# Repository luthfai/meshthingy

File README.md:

# meshthingy

> An off-grid LoRa mesh communicator — a pocket-sized ESP32-S3 node that sends
> text and GPS position over kilometres of open ground, with no cell tower, no
> SIM, no subscription, and no internet.

<sub>KiCad 10 · 2-layer · 71 × 46 mm · ESP32-S3 + SX1262 LoRa · USB-C · Li-Ion · hardware rev R1</sub>

> [!WARNING]
> **Rev R1 is currently in fabrication — nothing here has been tested yet.**
> The schematic and layout are finished and pass DRC, but no board has been
> assembled or powered up. Everything in this README (pin map, charger settings,
> power latch behaviour, assembly notes) describes the design *as intended* and
> may change after bring-up. Build one at your own risk.

## Project status

| Stage | Status |
| --- | --- |
| Schematic | ✅ Done |
| PCB layout | ✅ Done — 0 DRC violations, 0 unconnected items |
| BOM | ✅ Done — a few part variants still to pick (see [Bill of materials](#bill-of-materials)) |
| PCB fabrication | ⏳ In progress |
| Assembly | ⬜ Not started |
| Bring-up and testing | ⬜ Not started |
| Firmware | 🚧 Work in progress |

---

## What this board is for

Phones stop working the moment you leave coverage. **meshthingy** doesn't need
coverage — it *is* the network.

Each board is one node in a self-healing [Meshtastic](https://meshtastic.org)
mesh. Nodes talk directly to each other over licence-free LoRa radio, and every
node automatically relays traffic for its neighbours. Two units give you a
private long-range walkie-talkie for text; a handful scattered across a valley,
a campsite, a ridgeline, or a city block give everyone in that area a shared
messaging network that keeps working when nothing else does.

Because LoRa trades bandwidth for range and power, a node runs for **days** on a
small Li-Ion cell and reaches **several kilometres** line-of-sight — far past
Wi-Fi or Bluetooth, and without the power budget a cellular radio demands.

Typical uses: hiking and backcountry trips, sailing, off-road convoys, festival
and event crews, neighbourhood emergency preparedness, and as a low-cost
long-range telemetry link for remote sensors.

The onboard GPS, environmental and motion sensors mean a node is useful even
with nobody holding it — drop one on a hilltop as a solar-powered repeater and
it becomes a weather station that also extends everyone's range.

## Features

- **ESP32-S3-WROOM-1** — dual-core MCU with Wi-Fi and Bluetooth LE for phone pairing, native USB
- **HT-RA62 LoRa module** (SX1262) — long-range sub-GHz radio on an SMA edge-mount connector
- **ATGM336H GNSS** — position reporting on a U.FL active antenna, with a rechargeable backup cell for warm starts
- **0.96" OLED** — read messages without a phone
- **BME280** — temperature, humidity, barometric pressure, on a slotted island away from board heat
- **LIS3DSH accelerometer** — wake-on-motion and orientation, with interrupt to the MCU
- **USB-C charging** — BQ24072 Li-Ion charger with power-path, so it runs while charging
- **Soft power switch** — the lever's push turns the node on; firmware holds power and can turn itself off
- **JST-PH battery connector** — standard single-cell Li-Ion / LiPo, polarity marked on the silkscreen
- **Vibration motor driver** — SI2302 low-side switch with flyback diode, for silent alerts in a pocket
- **Buzzer, status LED, and a side lever switch** (CW / CCW / push) for headless operation
- **Test points** on every bus for bring-up and debugging

## System architecture

```mermaid
flowchart TB
    subgraph RF["📡 Radio"]
        LORA["<b>U4 · HT-RA62</b><br/>SX1262 LoRa"]
        SMA["J4 · SMA<br/>edge mount"]
        LORA --- SMA
    end

    subgraph CORE["🧠 Core"]
        MCU["<b>U7 · ESP32-S3-WROOM-1</b><br/>Wi-Fi · BLE · dual core"]
    end

    subgraph NAV["🛰️ Navigation"]
        GPS["<b>U2 · ATGM336H</b><br/>GNSS receiver"]
        UFL["J3 · U.FL<br/>active antenna"]
        EEP["U8 · AT24CS32<br/>EEPROM"]
        BAT2["C13 · XH414H<br/>backup cell"]
        UFL --- GPS
        GPS -->|"private I²C"| EEP
        BAT2 -.->|"keeps time"| GPS
    end

    subgraph IO["🔌 I²C peripherals"]
        OLED["U1 · 0.96in OLED"]
        BME["U9 · BME280<br/>temp · humidity · pressure"]
        ACC["U10 · LIS3DSH<br/>accelerometer"]
    end

    subgraph UX["🎛️ Interface"]
        BUZ["LS1 · buzzer"]
        LED["D2 · status LED"]
        SW["U5 · lever switch"]
        VIB["Q4 · SI2302<br/>vibration motor"]
    end

    MCU <==>|"<b>SPI</b> + BUSY/RST/DIO1"| LORA
    MCU <-->|"<b>UART</b> + 1PPS"| GPS
    MCU <-->|"<b>I²C</b> · IO13/IO14"| OLED
    MCU <-->|"<b>I²C</b>"| BME
    MCU <-->|"<b>I²C</b> + INT→IO48"| ACC
    MCU -->|IO16| BUZ
    MCU -->|IO21| LED
    MCU -->|IO15| VIB
    SW -->|"IO10/11/12"| MCU

    classDef core fill:#4f46e5,stroke:#3730a3,color:#fff,stroke-width:2px
    classDef radio fill:#0891b2,stroke:#0e7490,color:#fff
    classDef nav fill:#059669,stroke:#047857,color:#fff
    classDef periph fill:#d97706,stroke:#b45309,color:#fff
    classDef ux fill:#7c3aed,stroke:#6d28d9,color:#fff
    class MCU core
    class LORA,SMA radio
    class GPS,UFL,EEP,BAT2 nav
    class OLED,BME,ACC periph
    class BUZ,LED,SW,VIB ux
```

## Power path

USB-C and the battery both feed a power-path charger, so the node keeps running
while it charges and switches over seamlessly when USB is unplugged. The 3.3 V
buck converter is only enabled while something holds the power latch on.

```mermaid
flowchart LR
    USB["<b>J1</b><br/>USB-C<br/>5 V in"] -->|VBUS| CHG
    BATT["<b>J2</b><br/>Li-Ion cell<br/>JST-PH"] <-->|charge / discharge| CHG
    CHG["<b>U6 · BQ24072</b><br/>Li-Ion charger<br/>+ power path"] -->|VSYS| BUCK
    LATCH["<b>Power latch</b><br/>Q2 · Q3"] -->|BUCK_EN| BUCK
    BUCK["<b>U3 · TPS62046</b><br/>3.3 V step-down<br/>via L2"] -->|"+3V3"| RAIL

    BTN["Lever push"] -.-> LATCH
    PG["USB present<br/>(PGOOD)"] -.-> LATCH
    HOLD["IO9 · SYS_EN<br/>(firmware hold)"] -.-> LATCH

    RAIL["<b>+3V3 rail</b>"] --> M1["ESP32-S3"]
    RAIL --> M2["LoRa"]
    RAIL --> M3["GNSS"]
    RAIL --> M4["Sensors + OLED"]
    RAIL --> M5["Buzzer + vib motor"]

    classDef src fill:#dc2626,stroke:#991b1b,color:#fff,stroke-width:2px
    classDef conv fill:#ea580c,stroke:#c2410c,color:#fff,stroke-width:2px
    classDef rail fill:#16a34a,stroke:#15803d,color:#fff,stroke-width:2px
    classDef load fill:#475569,stroke:#334155,color:#fff
    classDef ctl fill:#64748b,stroke:#475569,color:#fff
    class USB,BATT src
    class CHG,BUCK conv
    class RAIL rail
    class M1,M2,M3,M4,M5 load
    class LATCH,BTN,PG,HOLD ctl
```

### Turning on and off

The buck converter's enable is driven by a PNP switch (`Q2`) from a latch node
that is pulled low by any one of three sources, each isolated by a 1N4148WS:

1. **Lever push** (`U5`, `D7`) — pressing it powers the board up.
2. **USB present** (`PGOOD` from `U6`, `D4`) — the node is always on while plugged in.
3. **Firmware hold** (`IO9` / `SYS_EN` through `Q3`) — firmware must drive IO9 high
   early in boot, or the board switches off again when the lever is released.
   Driving IO9 low (with USB unplugged) powers the node down.

The MCU can read the lever push on `IO10` and USB presence on `IO17` (both through
diodes, active low, use internal pull-ups). The latch diodes must stay
low-leakage silicon parts — Schottkys leak enough to half-enable the buck when off.

### Charger settings (U6 · BQ24072)

| Setting | Part | Value |
| --- | --- | --- |
| Fast-charge current | `R4` = 1k (1%) | ≈ 890 mA |
| USB input current limit | `R5` = 1k2, EN2 = 1 / EN1 = 0 | ≈ 1.34 A |
| Safety timers | `R6` = 47k | pre-charge ≈ 38 min, fast charge ≈ 6.3 h |
| Termination | `TD` tied low | enabled |
| Battery temperature | `R3` = 10k fixed on `TS` | no thermistor, sensing disabled |
| Charge enable | `IO18` (`R7` pull-down) | low = charging allowed |

`VSYS` follows the battery (and tracks VBAT + 225 mV while charging). `IO8` reads
`VSYS / 2` through `R16`/`R17` — that is the battery voltage when running on battery.

## Board

| | |
| --- | --- |
| **Dimensions** | 71.0 × 46.0 mm, cut-out under the ESP32 antenna, milled slots isolating the BME280 |
| **Stackup** | 2 layers (F.Cu / B.Cu), 1.6 mm |
| **Components** | 96 footprints, 353 pads (329 SMD, 22 through-hole, 2 NPTH), 378 vias |
| **Density** | 66% front, 9% back — almost everything lives on the front |
| **Copper** | GND pour on both layers, pour cut back under the RF connectors and antennas |
| **Design rules** | 0.175 mm clearance, 0.2 mm minimum track, 0.6 / 0.3 mm vias |
| **Assembly** | SMD on the front, 0805 passives; through-hole only for `J2`, the OLED header and the USB-C shell tabs |

Everything routes on two layers, which keeps this a cheap board to order from any
prototype fab at standard tolerances.

### Assembled views

<table>
  <tr>
    <td width="50%" align="center">
      <br>
      <sub><b>Front</b> — LoRa and GNSS modules, ESP32-S3, USB-C, buzzer, GPS backup cell, motor driver</sub>
    </td>
    <td width="50%" align="center">
      <br>
      <sub><b>Back</b> — labelled test points for every bus, vibration motor pads (<code>JP1</code>, silkscreen <code>VBR</code>), repo QR code</sub>
    </td>
  </tr>
</table>

### PCB layer views

Copper, silkscreen and board outline, plotted straight from the layout. The back
view is mirrored so its silkscreen reads the right way round.

<table>
  <tr>
    <td width="50%" align="center">
      <br>
      <sub><b>F.Cu + F.SilkS</b> — signal routing over the front ground pour; <code>B</code>/<code>R</code> are the boot and reset pads</sub>
    </td>
    <td width="50%" align="center">
      <br>
      <sub><b>B.Cu + B.SilkS</b> — mirrored; back pour with the test-point field and motor pads</sub>
    </td>
  </tr>
</table>

The RF section is deliberately sparse: the pours are cut back under the antenna
connectors, the ESP32's PCB antenna hangs over a board cut-out, and the GPS
keepout is marked on the silkscreen so nothing gets placed under it during assembly.

Regenerate the 3D renders and layer plots after any layout change (the renders
are trimmed with ImageMagick):

```bash
kicad-cli pcb render --output /tmp/f.png --side top    --quality high --width 2000 --height 1300 meshthingy.kicad_pcb
kicad-cli pcb render --output /tmp/b.png --side bottom --quality high --width 2000 --height 1300 meshthingy.kicad_pcb
magick /tmp/f.png -trim +repage -bordercolor none -border 24 docs/meshthingy-f.png
magick /tmp/b.png -trim +repage -bordercolor none -border 24 docs/meshthingy-b.png

kicad-cli pcb export svg --output docs/layers-front.svg \
  --layers "F.Cu,F.SilkS,Edge.Cuts" \
  --page-size-mode 2 --exclude-drawing-sheet --check-zones --mode-single \
  meshthingy.kicad_pcb

kicad-cli pcb export svg --output docs/layers-back.svg \
  --layers "B.Cu,B.SilkS,Edge.Cuts" --mirror \
  --page-size-mode 2 --exclude-drawing-sheet --check-zones --mode-single \
  meshthingy.kicad_pcb
```

## Pin map

| Function | ESP32-S3 pin | Goes to |
| --- | --- | --- |
| LoRa SCK | GPIO43 (TXD0) | `U4` pin 12 SCK |
| LoRa MOSI | IO1 | `U4` pin 14 MOSI |
| LoRa MISO | IO2 | `U4` pin 13 MISO |
| LoRa CS | IO6 | `U4` pin 15 NSS |
| LoRa DIO1 | IO4 | `U4` pin 6 (IRQ) |
| LoRa RESET | IO5 | `U4` pin 4 |
| LoRa BUSY | GPIO44 (RXD0) | `U4` pin 10 |
| GPS TX → MCU RX | IO42 | `U2` TXD |
| GPS RX ← MCU TX | IO41 | `U2` RXD |
| GPS 1PPS | IO40 | `U2` 1PPS |
| GPS reset | IO38 | `U2` nRESET |
| GPS on/off | IO39 | `U2` ON/OFF |
| I²C SDA / SCL | IO13 / IO14 | OLED (0x3C), BME280 (0x76), LIS3DSH (0x1D) |
| Accelerometer INT | IO48 | `U10` INT1 |
| Lever push | IO10 | `U5` push, via `D6` (active low) |
| Lever CCW / CW | IO11 / IO12 | `U5` (active low, 100 nF debounce) |
| Power hold | IO9 | `Q3` via `R9` — drive high to stay on |
| USB present | IO17 | `U6` PGOOD via `D3` (active low) |
| Charge enable | IO18 | `U6` CE (low = charge) |
| Battery sense | IO8 (ADC1_CH7) | `VSYS / 2` |
| Vibration motor | IO15 | `Q4` gate (10k pull-down `R23`) |
| Buzzer | IO16 | `Q1` gate (10k pull-down `R11`) |
| Status LED | IO21 | `D2` via `R22` |
| USB D− / D+ | IO19 / IO20 | `J1` (native USB) |
| Boot / reset | IO0 / EN | `B` / `R` pads |
| Spare / test | IO7, IO47 | back-side test points `IO07`, `IO47` |

IO3, IO35–37, IO45 and IO46 are left unconnected (strapping pins and the
octal-PSRAM pins on R8 module variants).

## Schematic layout

The design is hierarchical — root sheet [meshthingy.kicad_sch](meshthingy.kicad_sch):

| Sheet | Contents |
| --- | --- |
| [Power Management](Power%20Management.kicad_sch) | BQ24072 charger, TPS62046 buck, power latch, battery sense |
| [Microcontroller](Microcontroller.kicad_sch) | ESP32-S3-WROOM-1, boot and reset pads |
| [LORA](LORA.kicad_sch) | HT-RA62 module and SMA antenna path |
| [GPS](GPS.kicad_sch) | ATGM336H, U.FL antenna input, EEPROM, backup cell |
| [Display](Display.kicad_sch) | 0.96" OLED and its pinout-select jumpers |
| [Air Sensors](Air%20Sensors.kicad_sch) | BME280 |
| [Accelerometer](Accelerometer.kicad_sch) | LIS3DSH |
| [Peripherals](Peripherals.kicad_sch) | Buzzer and vibration motor drivers, status LED, test points |
| [Connectors](Connectors.kicad_sch) | USB-C receptacle, JST-PH battery |

## Bill of materials

The curated BOM is [bom/meshthingy-bom.csv](bom/meshthingy-bom.csv): 36 board
lines / 76 placed parts, plus the off-board items (battery, antennas, vibration
motor). It adds manufacturer part numbers where the footprint fixes the part,
and a notes column with ratings and the reason behind each value.

Still to pin down before ordering parts:

- `U7` — pick the module variant (e.g. `-N8R2`, `-N16R8`). Avoid the 1.8 V `…V`
  variants: IO47 and IO48 are in use.
- `C16`, `C25` — voltage rating (≥ 10 V low-ESR tantalum).
- `U4` — `HT-RA62-HF` for 863–928 MHz, `HT-RA62-LF` for 433/470 MHz.

Test points and solder jumpers are left out — they are PCB features, not parts.

A print-ready A4 copy with kitting checkboxes and the open items highlighted is
rendered from the CSV with `python bom/render_bom_pdf.py` (needs `pip install weasyprint`)
and written to `bom/meshthingy-bom.pdf`. For hand assembly, open
[bom/ibom.html](bom/ibom.html) in a browser — an interactive BOM that highlights
each part's position on the board.

## Building it

Open [meshthingy.kicad_pro](meshthingy.kicad_pro) in **KiCad 10** or newer.
All custom symbols and footprints live in [libs/](libs/) and are referenced through
`${KIPRJMOD}`, so the project is self-contained — clone and open, nothing else to install.

Generate fabrication files from the command line:

```bash
# Gerbers + drill, ready to zip and upload to a fab
kicad-cli pcb export gerbers --output fab/ meshthingy.kicad_pcb
kicad-cli pcb export drill   --output fab/ meshthingy.kicad_pcb

# Raw schematic BOM and pick-and-place
kicad-cli sch export bom       --output fab/bom-raw.csv meshthingy.kicad_sch
kicad-cli pcb export pos       --output fab/pos.csv meshthingy.kicad_pcb

# Design rules check
kicad-cli pcb drc --output fab/drc.rpt meshthingy.kicad_pcb
```

Generated outputs are gitignored — regenerate them, or attach them to a release tag.

### Assembly notes

`U3` (TPS62046) has a PowerPAD that must be soldered to the ground pad under it.
The pad is a copper shape on the board rather than part of the footprint, so it has
no paste aperture — tin it by hand, or add paste to the stencil, before reflowing U3.

`JP3` and `JP4` are three-way solder jumpers that select which OLED pin gets
`+3V3` and which gets `GND`, so the footprint accepts display modules with either
pinout. They ship **unbridged** — bridge them to match the module you source
before expecting the display to light up. Never bridge all three pads of one jumper.

`JP1` on the back (silkscreen `VBR`) is not a jumper. It's the pair of solder pads for the vibration
motor. Solder a coin or pager-style motor's leads across it: the pad on the
`+3V3` side takes the red lead and the pad on the `Q4` drain side takes the black
lead. `D9` clamps the motor's flyback, so the motor runs straight off the
`+3V3` rail.

`J2` has `+` / `−` marked on both sides. JST-PH battery leads are not wired the same
way by every vendor, and there is no reverse-polarity protection — check the plug
before connecting a cell.

`B` and `R` on the front are the **BOOT** and **RESET** pads. To put the ESP32-S3
into the ROM bootloader, short `B` while you tap `R`.

## Firmware

🚧 **Work in progress.** There is no firmware for this board yet — it will target
[Meshtastic](https://meshtastic.org) on the ESP32-S3 once the first boards are
back from the fab and brought up. Until then, the [pin map](#pin-map) above is
the reference for anyone writing a variant.

## Repository notes

`.history/` is KiCad 10's Local History — a separate nested git repository of
autosaves. It is gitignored and should stay that way. Delete it freely if you
don't need the local undo history.

---

<sub>Meshtastic® is a registered trademark of Meshtastic LLC. This is an
independent hardware design and is not affiliated with or endorsed by Meshtastic LLC.</sub>

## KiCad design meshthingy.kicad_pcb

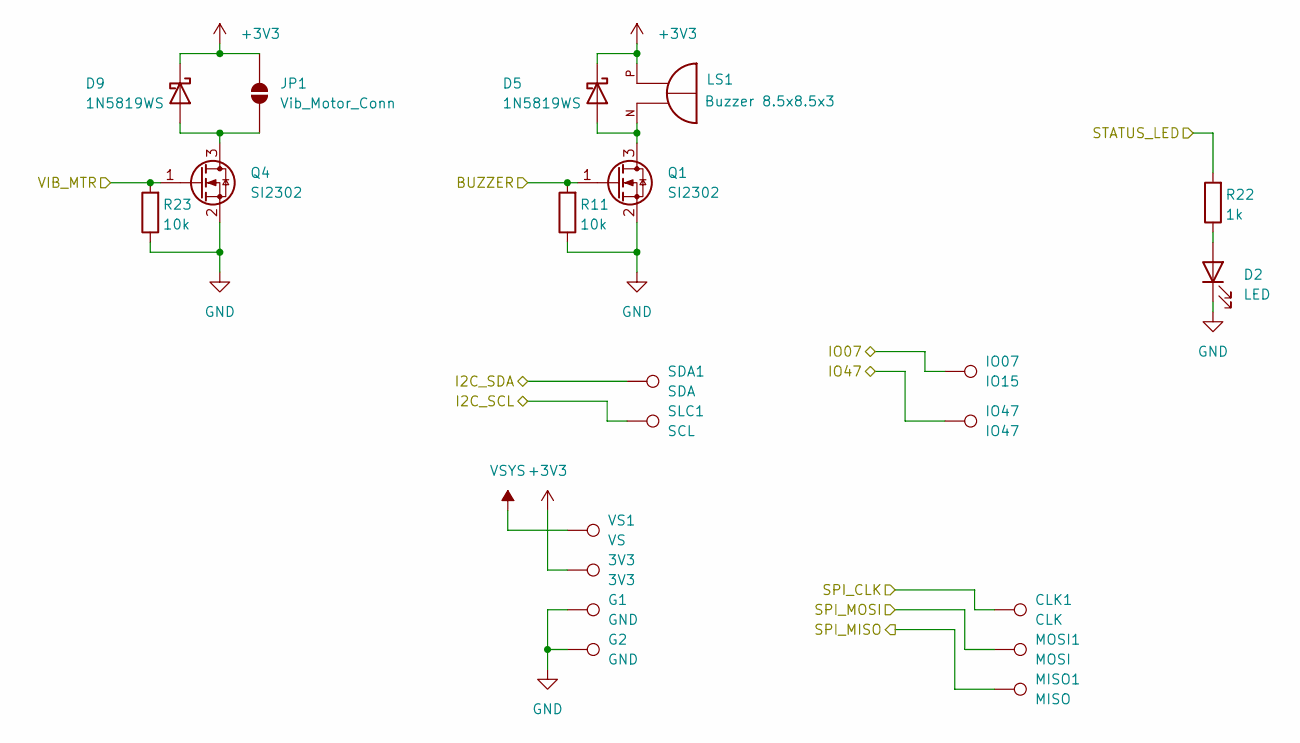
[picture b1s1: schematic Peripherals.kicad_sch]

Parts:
3V3: 3V3; TestPoint_Pad_1.0x1.0mm
CLK1: CLK; TestPoint_Pad_1.0x1.0mm
D2: LED; LED_0805_2012Metric
D5, D9: 1N5819WS; D_SOD-323
G1, G2: GND; TestPoint_Pad_1.0x1.0mm
IO07: IO15; TestPoint_Pad_1.0x1.0mm
IO47: IO47; TestPoint_Pad_1.0x1.0mm
JP1: Vib_Motor_Conn; SolderJumper-2_P1.3mm_Open_Pad1.0x1.5mm
LS1: Buzzer 8.5x8.5x3; XDCR_SMT-0927-S-14-R; PARTREV A
MISO1: MISO; TestPoint_Pad_1.0x1.0mm
MOSI1: MOSI; TestPoint_Pad_1.0x1.0mm
Q1, Q4: SI2302; SOT-23
R11, R23: 10k; R_0805_2012Metric
R22: 1k; R_0805_2012Metric
SDA1: SDA; TestPoint_Pad_1.0x1.0mm
SLC1: SCL; TestPoint_Pad_1.0x1.0mm
VS1: VS; TestPoint_Pad_1.0x1.0mm

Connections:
+3V3: 3V3.1 (1_1), D5.1 (K), D9.1 (K), JP1.2 (B), LS1.P; also elsewhere on the board
/Accelerometer/SCL: SLC1.1 (1_1); also elsewhere on the board
/Accelerometer/SDA: SDA1.1 (1_1); also elsewhere on the board
/LORA/SPI2_CLK: CLK1.1 (1_1); also elsewhere on the board
/LORA/SPI2_MISO: MISO1.1 (1_1); also elsewhere on the board
/LORA/SPI2_MOSI: MOSI1.1 (1_1); also elsewhere on the board
/Microcontroller/BUZZER: Q1.1 (G), R11.2; also elsewhere on the board
/Microcontroller/IO07: IO07.1 (1_1); also elsewhere on the board
/Microcontroller/IO47: IO47.1 (1_1); also elsewhere on the board
/Microcontroller/STATUS_LED: R22.2; also elsewhere on the board
/Microcontroller/VIB_MTR: Q4.1 (G), R23.2; also elsewhere on the board
GND: D2.1 (K), G1.1 (1_1), G2.1 (1_1), Q1.2 (S), Q4.2 (S), R11.1, R23.1; also elsewhere on the board
unnamed: D2.2 (A), R22.1
unnamed: D5.2 (A), LS1.N, Q1.3 (D)
unnamed: D9.2 (A), JP1.1 (A), Q4.3 (D)
VSYS: VS1.1 (1_1); also elsewhere on the board

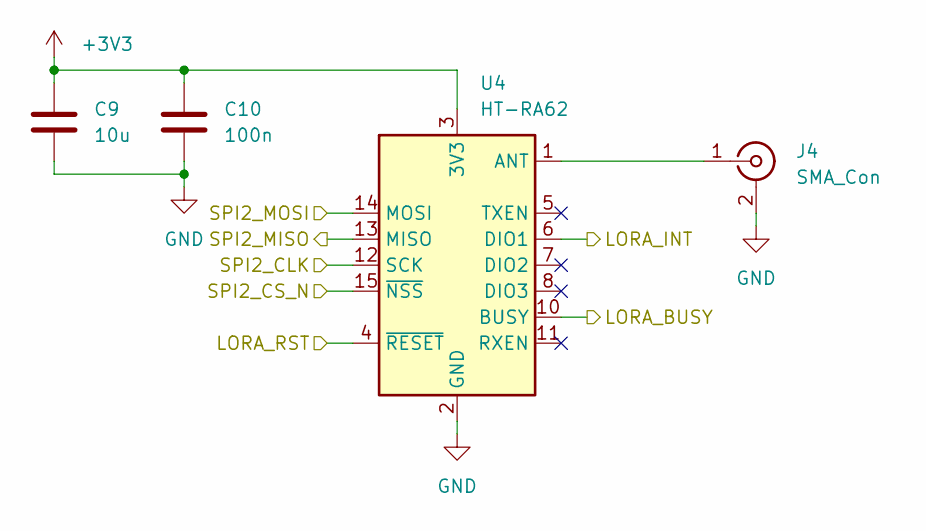
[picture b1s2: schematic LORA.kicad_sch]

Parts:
C9: 10u; C_0805_2012Metric
C10: 100n; C_0805_2012Metric
J4: SMA_Con; SMA_Amphenol_132289_EdgeMount
U4: HT-RA62; Ai-Thinker-Ra-01-LoRa

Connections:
+3V3: C9.1, C10.1, U4.3 (3V3); also elsewhere on the board
/LORA/LORA_BUSY: U4.10 (BUSY); also elsewhere on the board
/LORA/LORA_INT: U4.6 (DIO1); also elsewhere on the board
/LORA/LORA_RST: U4.4 (~RESET); also elsewhere on the board
/LORA/SPI2_CLK: U4.12 (SCK); also elsewhere on the board
/LORA/SPI2_CS_N: U4.15 (~NSS); also elsewhere on the board
/LORA/SPI2_MISO: U4.13 (MISO); also elsewhere on the board
/LORA/SPI2_MOSI: U4.14 (MOSI); also elsewhere on the board
GND: C9.2, C10.2, J4.2 (Ext), U4.2 (GND), U4.9 (GND), U4.16 (GND); also elsewhere on the board
unnamed: J4.1 (In), U4.1 (ANT)

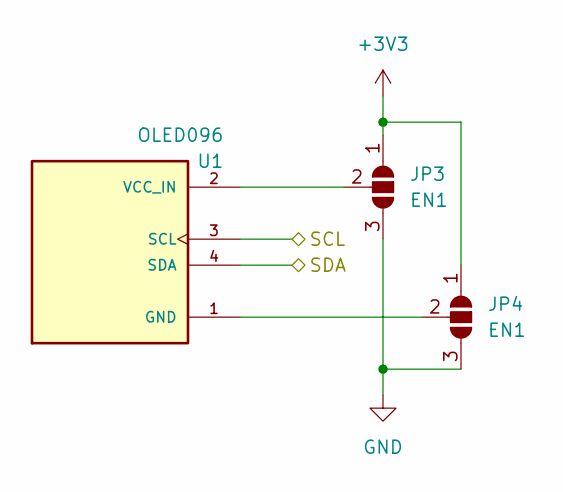
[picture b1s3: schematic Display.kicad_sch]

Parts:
JP3, JP4: EN1; SolderJumper-3_P1.3mm_Open_Pad1.0x1.5mm
U1: OLED096; MODULE_DM-OLED096-636; PARTREV 2018-09-10

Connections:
+3V3: JP3.1 (A), JP4.1 (A); also elsewhere on the board
/Accelerometer/SCL: U1.3 (SCL); also elsewhere on the board
/Accelerometer/SDA: U1.4 (SDA); also elsewhere on the board
GND: JP3.3 (B), JP4.3 (B); also elsewhere on the board
unnamed: JP3.2 (C), U1.2 (VCC_IN)
unnamed: JP4.2 (C), U1.1 (GND)

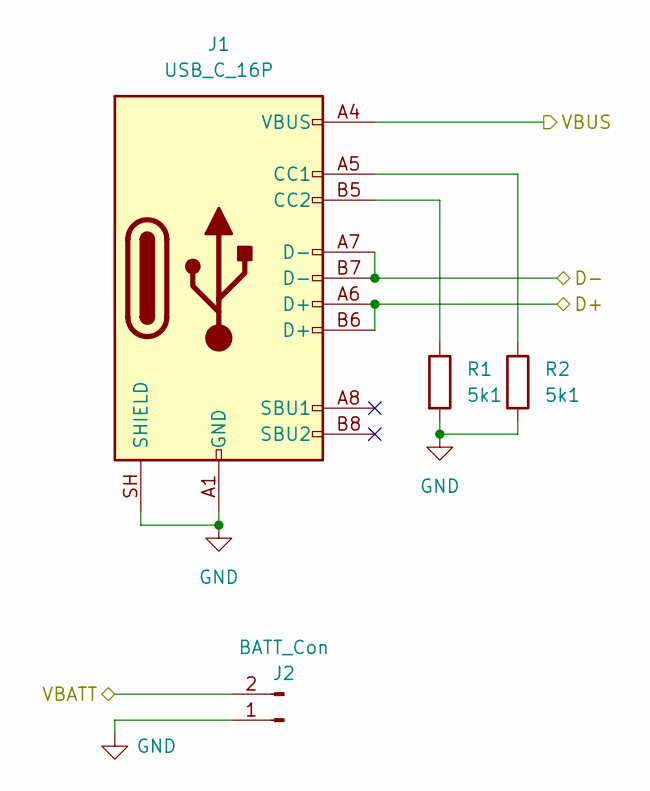
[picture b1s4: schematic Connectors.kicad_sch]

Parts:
J1: USB_C_16P; USB_C_Receptacle_G-Switch_GT-USB-7010ASV
J2: BATT_Con; JST_PH_S2B-PH-K_1x02_P2.00mm_Horizontal
R1, R2: 5k1; R_0805_2012Metric

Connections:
/Connectors/D+: J1.A6 (D+), J1.B6 (D+); also elsewhere on the board
/Connectors/D-: J1.A7 (D-), J1.B7 (D-); also elsewhere on the board
/Connectors/VBATT: J2.2; also elsewhere on the board
/Connectors/VBUS: J1.A4 (VBUS), J1.A9 (VBUS), J1.B4 (VBUS), J1.B9 (VBUS); also elsewhere on the board
GND: J1.A1 (GND), J1.A12 (GND), J1.B1 (GND), J1.B12 (GND), J1.SH (SHIELD), J2.1, R1.2, R2.2; also elsewhere on the board
unnamed: J1.A5 (CC1), R2.1
unnamed: J1.B5 (CC2), R1.1

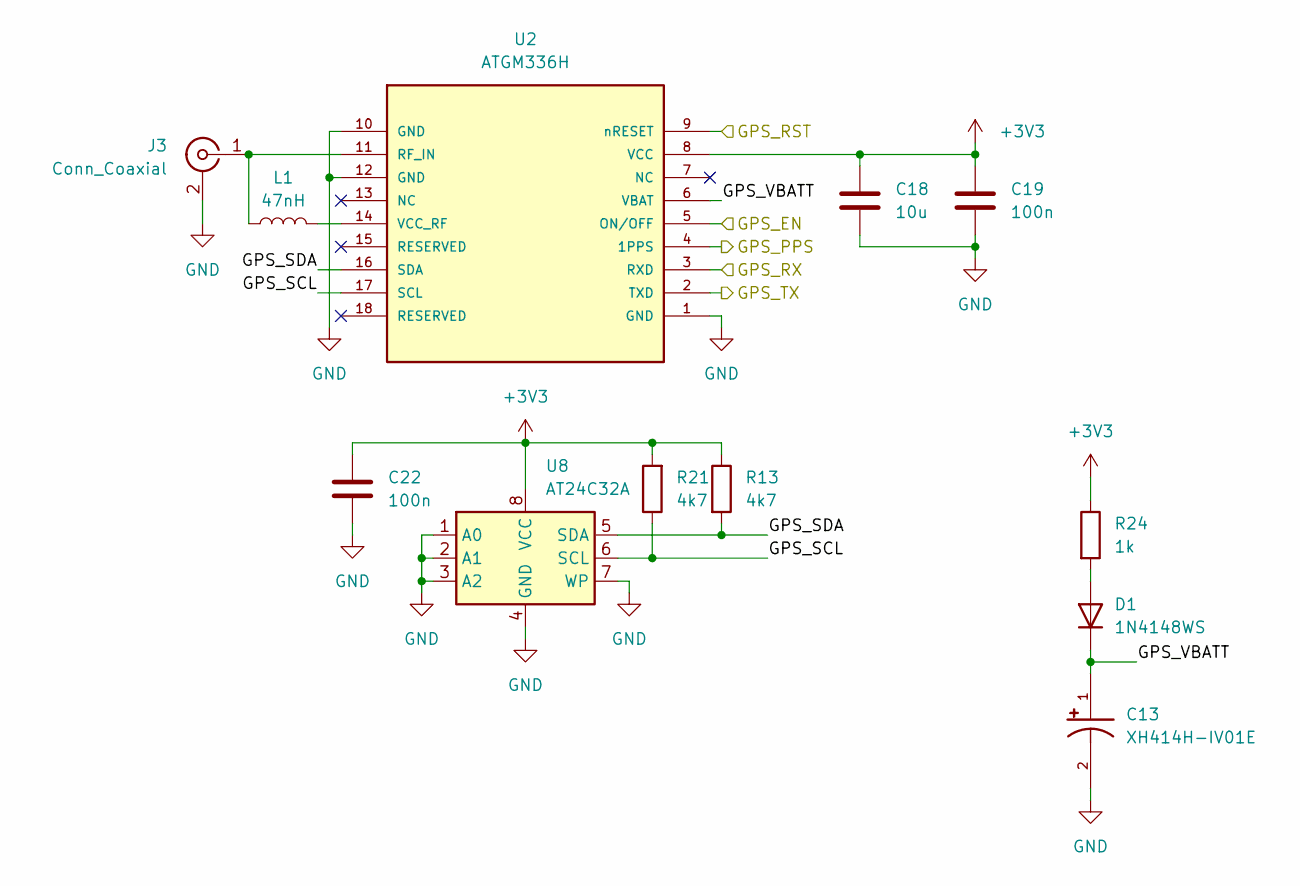
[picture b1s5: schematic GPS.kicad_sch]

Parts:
C13: XH414H-IV01E; CAP_XH414H-IV01E
C18: 10u; C_0805_2012Metric
C19, C22: 100n; C_0805_2012Metric
D1: 1N4148WS; D_SOD-323
J3: Conn_Coaxial; U.FL_Hirose_U.FL-R-SMT-1_Vertical
L1: 47nH; L_0402_1005Metric
R13, R21: 4k7; R_0805_2012Metric
R24: 1k; R_0805_2012Metric
U2: ATGM336H; ATGM336H-5N; LCSC C2940946
U8: AT24C32A; TSSOP-8_4.4x3mm_P0.65mm

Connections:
+3V3: C18.1, C19.1, C22.1, R13.1, R21.2, R24.1, U2.8 (VCC), U8.8 (VCC); also elsewhere on the board
/GPS/GPS_EN: U2.5 (ON/OFF); also elsewhere on the board
/GPS/GPS_PPS: U2.4 (1PPS); also elsewhere on the board
/GPS/GPS_RST: U2.9 (nRESET); also elsewhere on the board
/GPS/GPS_RX: U2.3 (RXD); also elsewhere on the board
/GPS/GPS_SCL: R21.1, U2.17 (SCL), U8.6 (SCL)
/GPS/GPS_SDA: R13.2, U2.16 (SDA), U8.5 (SDA)
/GPS/GPS_TX: U2.2 (TXD); also elsewhere on the board
/GPS/GPS_VBATT: C13.1, D1.1 (K), U2.6 (VBAT)
GND: C13.2, C18.2, C19.2, C22.2, J3.2 (Ext), U2.1 (GND), U2.10 (GND), U2.12 (GND), U8.1 (A0), U8.2 (A1), U8.3 (A2), U8.4 (GND), U8.7 (WP); also elsewhere on the board
unnamed: D1.2 (A), R24.2
unnamed: J3.1 (In), L1.1, U2.11 (RF_IN)
unnamed: L1.2, U2.14 (VCC_RF)

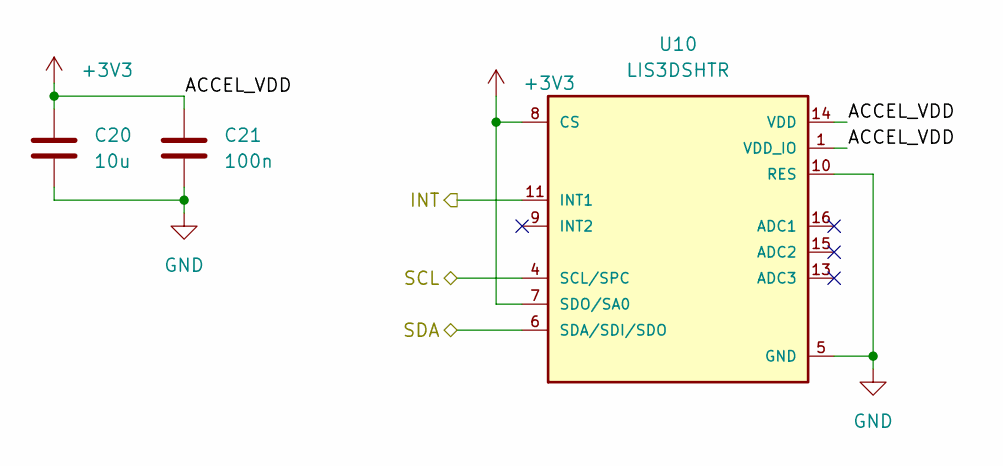
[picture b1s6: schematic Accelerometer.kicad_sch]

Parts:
C20: 10u; C_0805_2012Metric
C21: 100n; C_0805_2012Metric
U10: LIS3DSHTR; LGA16R50P5X3_300X300X100N

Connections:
+3V3: C20.1, C21.1, U10.1 (VDD_IO), U10.7 (SDO/SA0), U10.8 (CS), U10.14 (VDD); also elsewhere on the board
/Accelerometer/INT: U10.11 (INT1); also elsewhere on the board
/Accelerometer/SCL: U10.4 (SCL/SPC); also elsewhere on the board
/Accelerometer/SDA: U10.6 (SDA/SDI/SDO); also elsewhere on the board
GND: C20.2, C21.2, U10.5 (GND), U10.10 (RES), U10.12 (GND); also elsewhere on the board

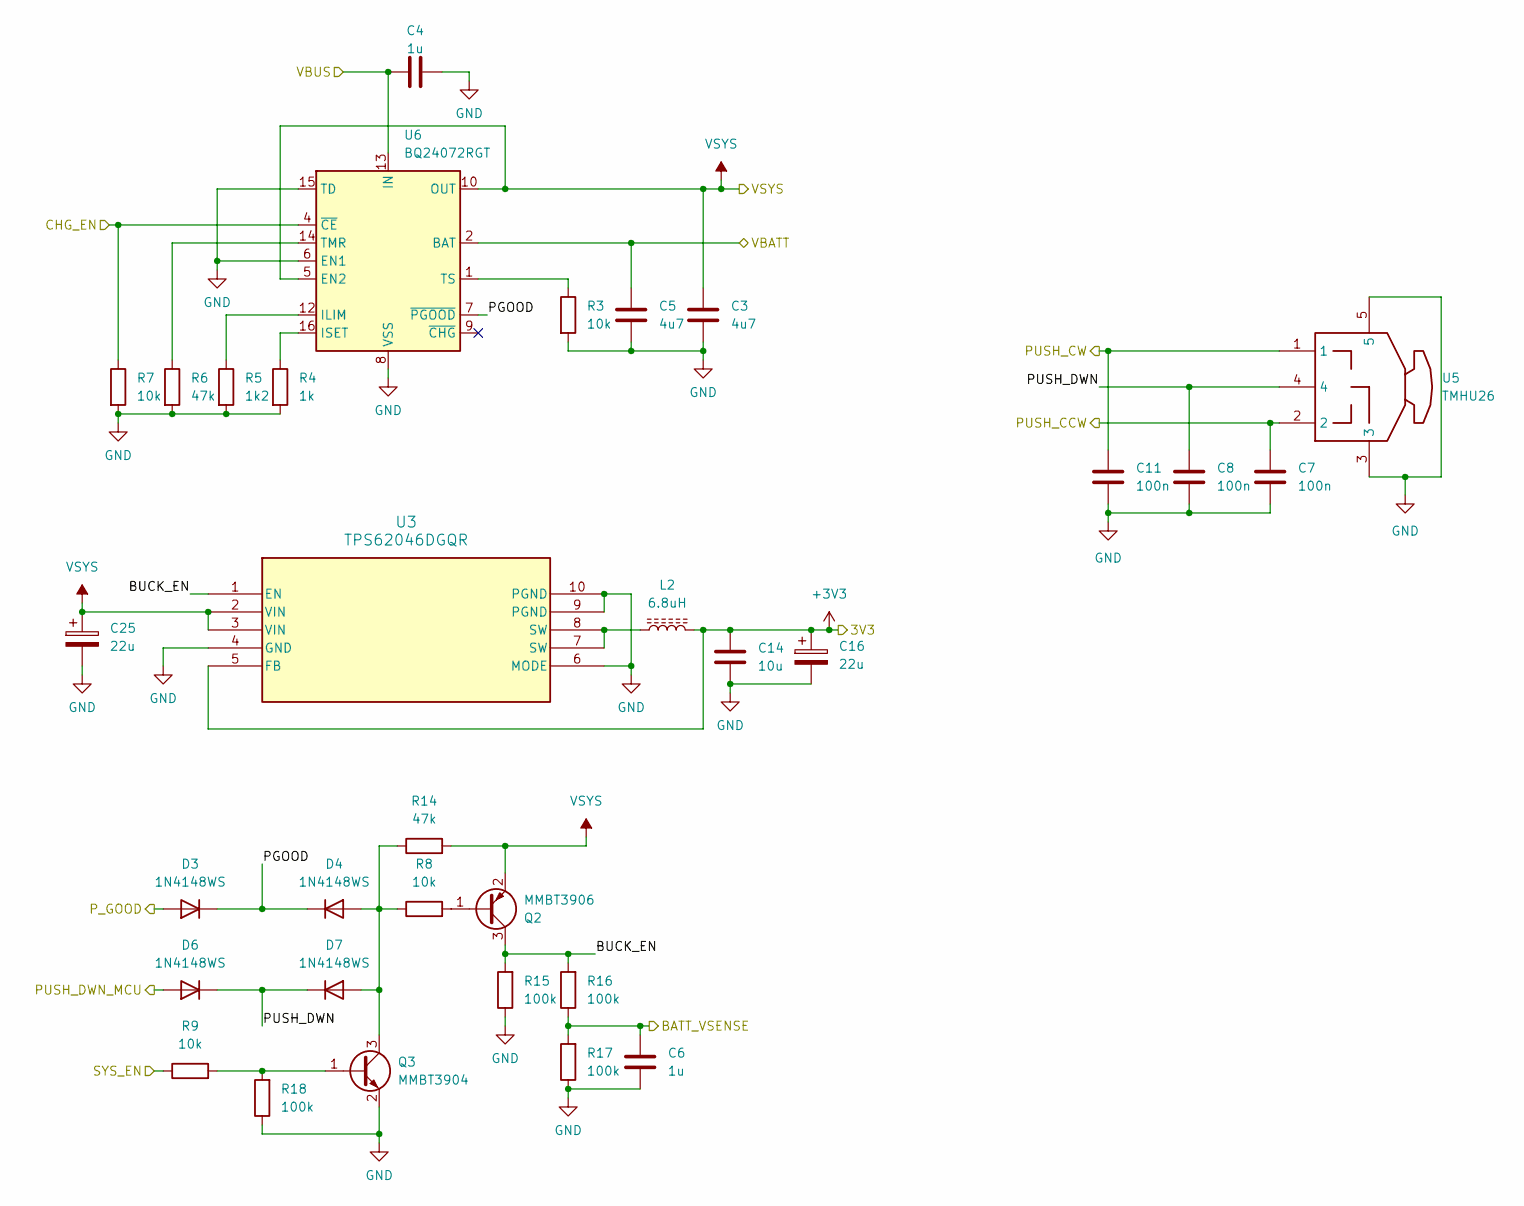
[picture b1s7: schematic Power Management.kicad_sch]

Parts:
C3, C5: 4u7; C_0805_2012Metric
C4, C6: 1u; C_0805_2012Metric
C7, C8, C11: 100n; C_0805_2012Metric
C14: 10u; C_0805_2012Metric
C16, C25: 22u; CP_EIA-3528-15_AVX-H
D3, D4, D6, D7: 1N4148WS; D_SOD-323
L2: 6.8uH; L_Changjiang_FNR6045S
Q2: MMBT3906; SOT-23
Q3: MMBT3904; SOT-23
R3, R7, R8, R9: 10k; R_0805_2012Metric
R4: 1k; R_0805_2012Metric
R5: 1k2; R_0805_2012Metric
R6, R14: 47k; R_0805_2012Metric
R15, R16, R17, R18: 100k; R_0805_2012Metric
U3: TPS62046DGQR; DGQ10_1P88X1P57
U5: TMHU26; tmhu26
U6: BQ24072RGT; VQFN-16-1EP_3x3mm_P0.5mm_EP1.6x1.6mm

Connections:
+3V3: C14.2, C16.1, L2.2, U3.5 (FB); also elsewhere on the board
/Connectors/VBATT: C5.1, U6.2 (BAT), U6.3 (BAT); also elsewhere on the board
/Connectors/VBUS: C4.2, U6.13 (IN); also elsewhere on the board
/Microcontroller/BAT_ADC: C6.1, R16.1, R17.2; also elsewhere on the board
/Microcontroller/CHG_EN: R7.1, U6.4 (~CE); also elsewhere on the board
/Microcontroller/PUSH_CCW: C7.1, U5.2; also elsewhere on the board
/Microcontroller/PUSH_CW: C11.1, U5.1; also elsewhere on the board
/Microcontroller/PUSH_DWN_MCU: D6.2 (A); also elsewhere on the board
/Microcontroller/P_GOOD: D3.2 (A); also elsewhere on the board
/Microcontroller/SYS_EN: R9.1; also elsewhere on the board
/Power Management/BUCK_EN: Q2.3 (C), R15.2, R16.2, U3.1 (EN)
/Power Management/PGOOD: D3.1 (K), D4.1 (K), U6.7 (~PGOOD)
/Power Management/PUSH_DWN: C8.1, D6.1 (K), D7.1 (K), U5.4
GND: C3.2, C4.1, C5.2, C6.2, C7.2, C8.2, C11.2, C14.1, C16.2, C25.2, Q3.2 (E), R3.2, R4.2, R5.2, R6.2, R7.2, R15.1, R17.1, R18.1, U3.4 (GND), U3.6 (MODE), U3.9 (PGND), U3.10 (PGND), U5.3, U5.5, U6.6 (EN1), U6.8 (VSS), U6.15 (TD), U6.17 (VSS); also elsewhere on the board
unnamed: D4.2 (A), D7.2 (A), Q3.3 (C), R8.1, R14.1
unnamed: L2.1, U3.7 (SW), U3.8 (SW)
unnamed: Q2.1 (B), R8.2
unnamed: Q3.1 (B), R9.2, R18.2
unnamed: R5.1, U6.12 (ILIM)
unnamed: R4.1, U6.16 (ISET)
unnamed: R6.1, U6.14 (TMR)
unnamed: R3.1, U6.1 (TS)
VSYS: C3.1, C25.1, Q2.2 (E), R14.2, U3.2 (VIN), U3.3 (VIN), U6.5 (EN2), U6.10 (OUT), U6.11 (OUT); also elsewhere on the board

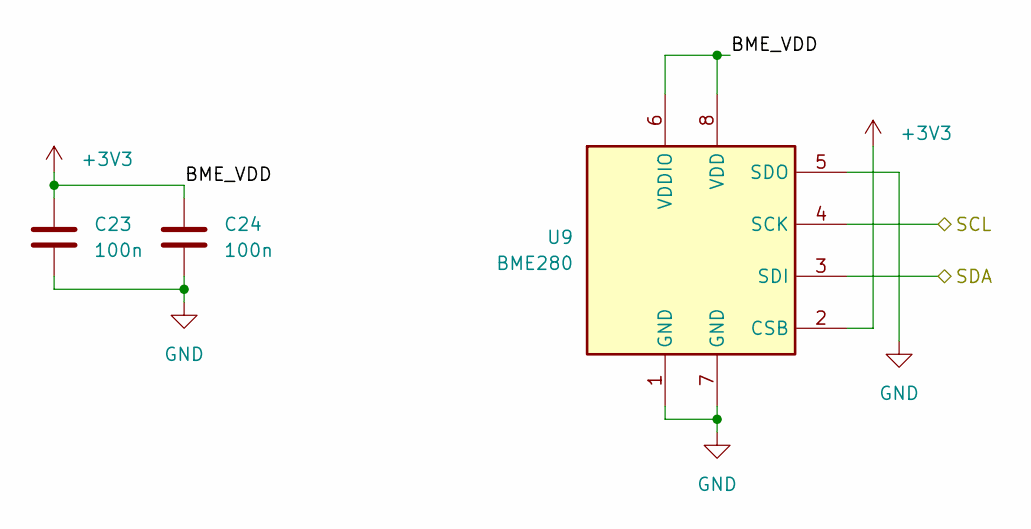
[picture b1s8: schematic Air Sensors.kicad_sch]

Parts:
C23, C24: 100n; C_0805_2012Metric
U9: BME280; Bosch_LGA-8_2.5x2.5mm_P0.65mm_ClockwisePinNumbering

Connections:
+3V3: C23.1, C24.1, U9.2 (CSB), U9.6 (VDDIO), U9.8 (VDD); also elsewhere on the board
/Accelerometer/SCL: U9.4 (SCK); also elsewhere on the board
/Accelerometer/SDA: U9.3 (SDI); also elsewhere on the board
GND: C23.2, C24.2, U9.1 (GND), U9.5 (SDO), U9.7 (GND); also elsewhere on the board

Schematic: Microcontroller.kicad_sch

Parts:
BOOT1: Boot; SolderJumper-2_P1.3mm_Open_Pad1.0x1.5mm
C1: 100n; C_0805_2012Metric
C2: 10u; C_0805_2012Metric
C17: 1u; C_0805_2012Metric
R10, R12: 4k7; R_0805_2012Metric
R19, R20: 10k; R_0805_2012Metric
RST1: Reset; SolderJumper-2_P1.3mm_Open_Pad1.0x1.5mm
U7: ESP32-S3-WROOM-1

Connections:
+3V3: C1.1, C2.1, R10.2, R12.1, R19.1, R20.1, U7.2 (3V3); also elsewhere on the board
/Accelerometer/INT: U7.25 (IO48); also elsewhere on the board
/Accelerometer/SCL: R10.1, U7.22 (IO14); also elsewhere on the board
/Accelerometer/SDA: R12.2, U7.21 (IO13); also elsewhere on the board
/Connectors/D+: U7.14 (USB_D+); also elsewhere on the board
/Connectors/D-: U7.13 (USB_D-); also elsewhere on the board
/GPS/GPS_EN: U7.32 (IO39); also elsewhere on the board
/GPS/GPS_PPS: U7.33 (IO40); also elsewhere on the board
/GPS/GPS_RST: U7.31 (IO38); also elsewhere on the board
/GPS/GPS_RX: U7.34 (IO41); also elsewhere on the board
/GPS/GPS_TX: U7.35 (IO42); also elsewhere on the board
/LORA/LORA_BUSY: U7.36 (RXD0); also elsewhere on the board
/LORA/LORA_INT: U7.4 (IO4); also elsewhere on the board
/LORA/LORA_RST: U7.5 (IO5); also elsewhere on the board
/LORA/SPI2_CLK: U7.37 (TXD0); also elsewhere on the board
/LORA/SPI2_CS_N: U7.6 (IO6); also elsewhere on the board
/LORA/SPI2_MISO: U7.38 (IO2); also elsewhere on the board
/LORA/SPI2_MOSI: U7.39 (IO1); also elsewhere on the board
/Microcontroller/BAT_ADC: U7.12 (IO8); also elsewhere on the board
/Microcontroller/BOOT: BOOT1.2 (B), R20.2, U7.27 (IO0)
/Microcontroller/BUZZER: U7.9 (IO16); also elsewhere on the board
/Microcontroller/CHG_EN: U7.11 (IO18); also elsewhere on the board
/Microcontroller/IO07: U7.7 (IO7); also elsewhere on the board
/Microcontroller/IO47: U7.24 (IO47); also elsewhere on the board
/Microcontroller/PUSH_CCW: U7.19 (IO11); also elsewhere on the board
/Microcontroller/PUSH_CW: U7.20 (IO12); also elsewhere on the board
/Microcontroller/PUSH_DWN_MCU: U7.18 (IO10); also elsewhere on the board
/Microcontroller/P_GOOD: U7.10 (IO17); also elsewhere on the board
/Microcontroller/RESET: C17.2, R19.2, RST1.2 (B), U7.3 (EN)
/Microcontroller/STATUS_LED: U7.23 (IO21); also elsewhere on the board
/Microcontroller/SYS_EN: U7.17 (IO9); also elsewhere on the board
/Microcontroller/VIB_MTR: U7.8 (IO15); also elsewhere on the board
GND: BOOT1.1 (A), C1.2, C2.2, C17.1, RST1.1 (A), U7.1 (GND), U7.40 (GND), U7.41 (GND); also elsewhere on the board

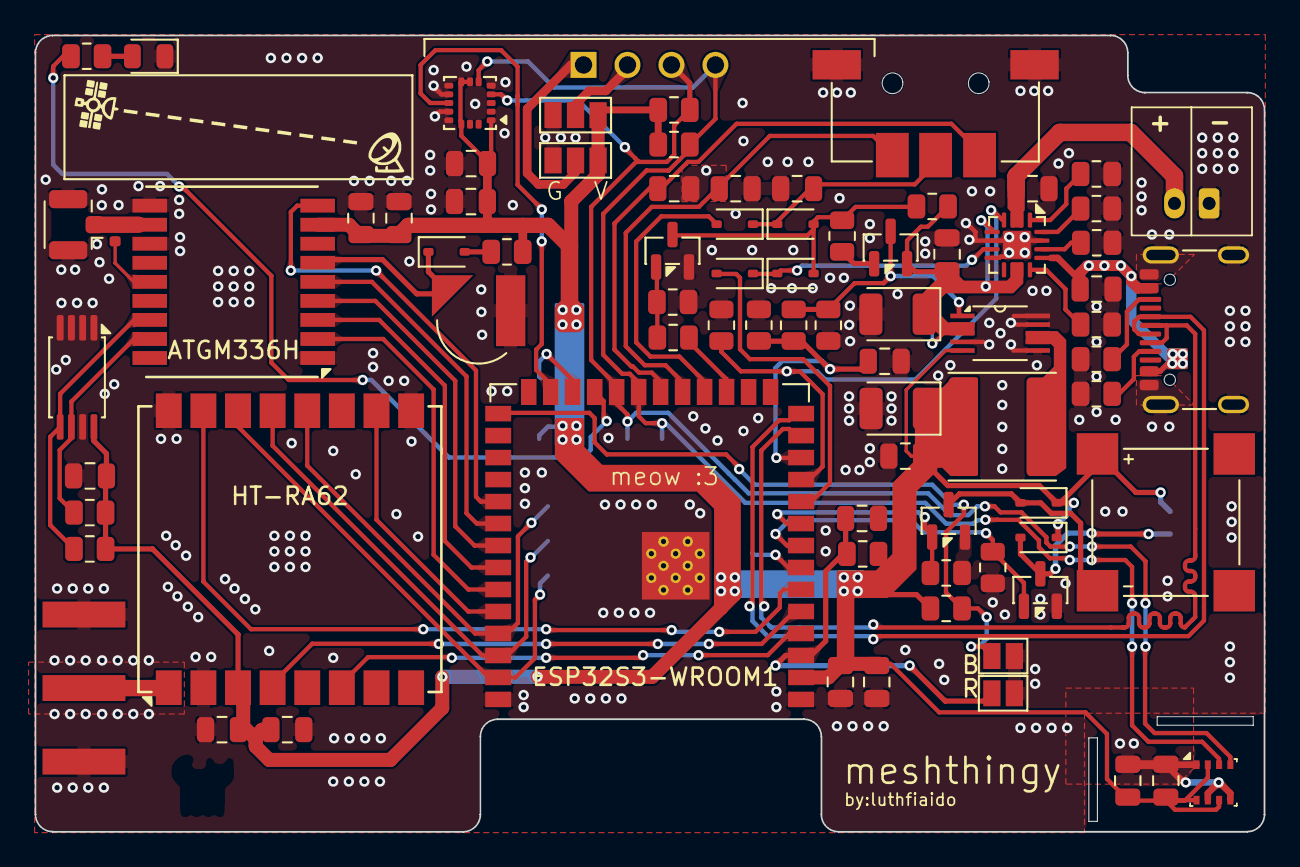
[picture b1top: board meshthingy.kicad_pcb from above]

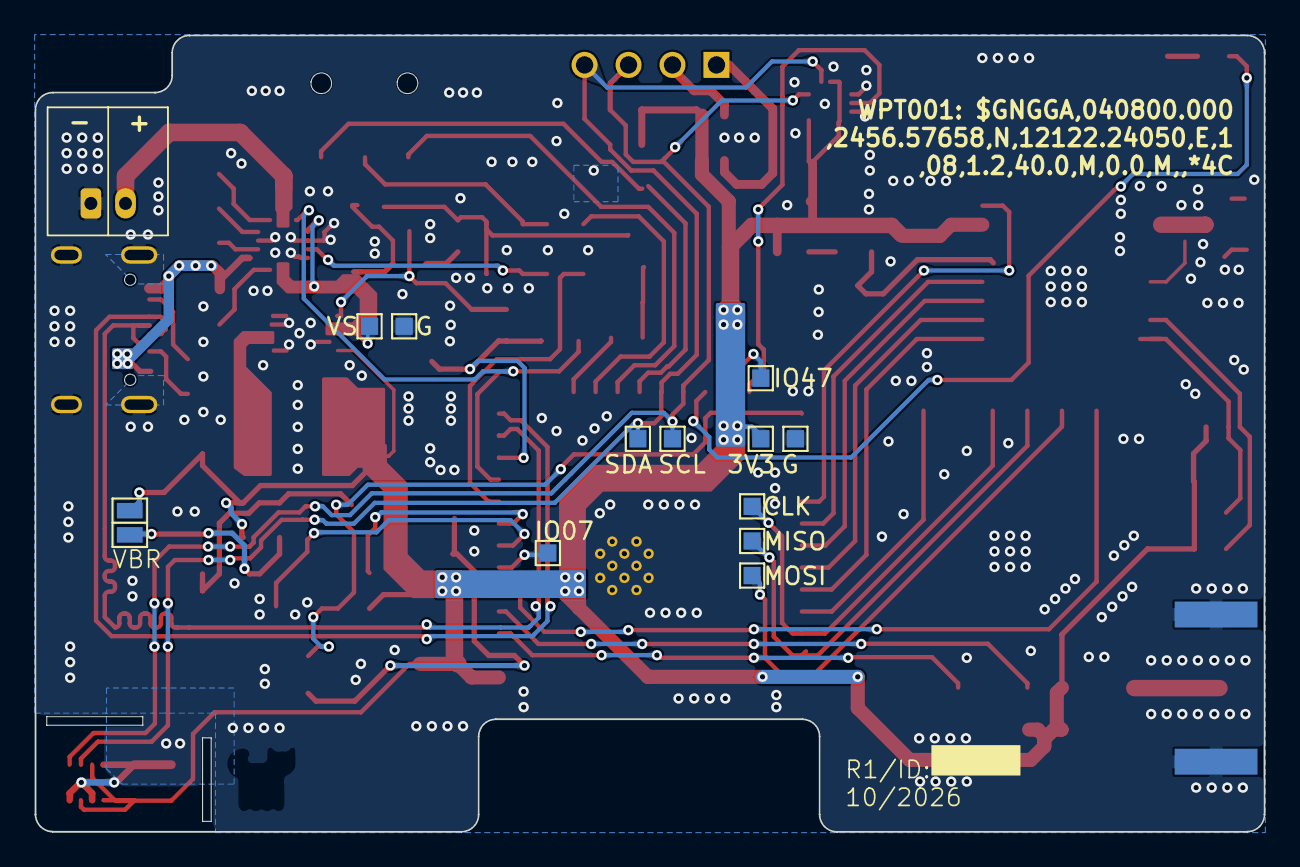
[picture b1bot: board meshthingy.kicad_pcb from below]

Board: 2 copper layers, 71.0 x 46.0 mm, 92 parts (12 on the bottom side), 61 nets.

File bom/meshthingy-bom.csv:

Item,Qty,Reference,Value,Description,Manufacturer,MPN,Footprint,Notes
1,10,"C1,C7,C8,C10,C11,C19,C21,C22,C23,C24",100n,Unpolarized capacitor,,,C_0805_2012Metric,"X7R, >=16 V"
2,5,"C2,C9,C14,C18,C20",10u,Unpolarized capacitor,,,C_0805_2012Metric,"X5R/X7R, >=10 V"
3,2,"C3,C5",4u7,Unpolarized capacitor,,,C_0805_2012Metric,"X5R/X7R, >=10 V (C5 on battery, C3 on VSYS)"
4,3,"C4,C6,C17",1u,Unpolarized capacitor,,,C_0805_2012Metric,X5R/X7R; C4 is on USB VBUS: use >=16 V
5,1,C13,XH414H-IV01E,"GPS backup cell, rechargeable 3.3 V coin",Seiko Instruments,XH414H-IV01E,CAP_XH414H-IV01E,GPS backup cell (rechargeable)
6,2,"C16,C25",22u,"Tantalum capacitor, 3528",,,CP_EIA-3528-15_AVX-H,TODO voltage rating: >=10 V low-ESR tantalum (VSYS up to 4.4 V; C25 sees battery hot-plug)
7,5,"D1,D3,D4,D6,D7",1N4148WS,"75V 0.15A Fast switching Diode, SOD-323",,,D_SOD-323,"D3/D4/D6/D7 power latch: low leakage required, do not substitute Schottky"
8,1,D2,LED,"LED, 0805",,,LED_0805_2012Metric,"Status LED, any colour (R22 = 1k)"
9,2,"D5,D9",1N5819WS,"40V 600mV@1A 1A SOD-323 Schottky Barrier Diodes, SOD-323",,,D_SOD-323,Flyback diodes for buzzer (D5) and vibration motor (D9)
10,1,J1,USB_C_16P,USB 2.0-only 16P Type-C Receptacle connector,G-Switch,GT-USB-7010ASV,USB_C_Receptacle_G-Switch_GT-USB-7010ASV,
11,1,J2,BATT_Con,"JST-PH 2-pin horizontal, battery",JST,S2B-PH-K-S,JST_PH_S2B-PH-K_1x02_P2.00mm_Horizontal,
12,1,J3,Conn_Coaxial,"U.FL receptacle, GPS antenna",Hirose,U.FL-R-SMT-1,U.FL_Hirose_U.FL-R-SMT-1_Vertical,
13,1,J4,SMA_Con,"SMA edge-mount jack, LoRa antenna",Amphenol RF,132289,SMA_Amphenol_132289_EdgeMount,
14,1,L1,47nH,"Inductor, 0402",,,L_0402_1005Metric,GPS active-antenna bias choke
15,1,L2,6.8uH,"Power inductor, 6x6 mm shielded",,,L_Changjiang_FNR6045S,"Buck inductor, Isat >= 1.5 A (e.g. Changjiang FNR6045S6R8MT)"
16,1,LS1,Buzzer 8.5x8.5x3,"Magnetic buzzer/transducer, 8.5 x 8.5 mm",PUI Audio,SMT-0927-S-14-R,XDCR_SMT-0927-S-14-R,"Magnetic transducer, PWM driven - verify exact MPN"
17,2,"Q1,Q4",SI2302,"N-channel MOSFET, SOT-23 (buzzer / motor driver)",,,SOT-23,"N-MOSFET, logic-level (Vgs(th) <= 1.5 V); e.g. Vishay SI2302CDS or equivalent"
18,1,Q2,MMBT3906,"PNP transistor, SOT-23 (buck enable switch)",,,SOT-23,Or BC857; SOT-23 pinout B-E-C
19,1,Q3,MMBT3904,"NPN transistor, SOT-23 (MCU power hold)",,,SOT-23,Or BC847; SOT-23 pinout B-E-C
20,2,"R1,R2",5k1,Resistor,,,R_0805_2012Metric,"USB-C CC pull-downs (Rd), 1%"
21,8,"R3,R7,R8,R9,R11,R19,R20,R23",10k,Resistor,,,R_0805_2012Metric,"R3 = BQ24072 TS bias (no thermistor), must stay 10k"
22,3,"R4,R22,R24",1k,Resistor,,,R_0805_2012Metric,"R4 = charge current ISET (890 mA), 1% required; R22 = LED; R24 = GPS backup charge"
23,1,R5,1k2,Resistor,,,R_0805_2012Metric,"ILIM: USB input current limit ~1.34 A, 1%"
24,2,"R6,R14",47k,Resistor,,,R_0805_2012Metric,R6 = charge safety timer (~6.3 h); R14 = power-latch pull-up
25,4,"R10,R12,R13,R21",4k7,Resistor,,,R_0805_2012Metric,"I2C pull-ups (R10/R12 main bus, R13/R21 GPS EEPROM bus)"
26,4,"R15,R16,R17,R18",100k,Resistor,,,R_0805_2012Metric,R16/R17 = VSYS/2 battery sense divider
27,1,U1,OLED096,0.96” 128 X 64 MONOCHROME GRAPHIC OLED DISPLAY MODULE - I2C,Display Module,DM-OLED096-636,MODULE_DM-OLED096-636,"0.96"" I2C OLED, 4-pin; set JP3/JP4 to match module pinout"
28,1,U2,ATGM336H,GNSS receiver module (GPS/BDS),Zhongke Microelectronics,ATGM336H-5N71,ATGM336H-5N,
29,1,U3,TPS62046DGQR,"1.2 A synchronous buck, fixed 3.3 V, MSOP-10 PowerPAD",Texas Instruments,TPS62046DGQR,DGQ10_1P88X1P57,Thermal pad must be soldered (paste or hand-solder)
30,1,U4,HT-RA62,"LoRa module, SX1262, SPI",Heltec Automation,HT-RA62-HF,Ai-Thinker-Ra-01-LoRa,"Choose HT-RA62-HF for 863-928 MHz, HT-RA62-LF for 433/470 MHz"
31,1,U5,TMHU26,"Lever / jog switch: CW, CCW, push",,,tmhu26,Push also powers the board on (via D7)
32,1,U6,BQ24072RGT,"Li-ion charger with power path, VQFN-16",Texas Instruments,BQ24072RGTR,VQFN-16-1EP_3x3mm_P0.5mm_EP1.6x1.6mm,
33,1,U7,ESP32-S3-WROOM-1,"ESP32-S3 module, Wi-Fi + BLE, PCB antenna",Espressif,ESP32-S3-WROOM-1-N?R? (TBD),ESP32-S3-WROOM-1,"TODO pick variant (e.g. -N8R2 / -N16R8). Do NOT use 1.8 V ""-V"" variants: IO47/IO48 are used"
34,1,U8,AT24C32A,"I2C EEPROM 32 Kbit, TSSOP-8 (GPS)",Microchip,AT24CS32-XHM-T,TSSOP-8_4.4x3mm_P0.65mm,"32 Kbit I2C EEPROM, TSSOP-8 (symbol is AT24CS32-XHM)"
35,1,U9,BME280,"Temperature / humidity / pressure sensor, LGA-8",Bosch Sensortec,BME280,Bosch_LGA-8_2.5x2.5mm_P0.65mm_ClockwisePinNumbering,
36,1,U10,LIS3DSHTR,"3-axis accelerometer, LGA-16",STMicroelectronics,LIS3DSHTR,LGA16R50P5X3_300X300X100N,
37,1,(JP1),Vibration motor,"Coin/pager vibration motor, 3 V",,,solder pads,"Not a schematic part. Red lead to +3V3 pad, black to Q4 drain pad"
38,1,(J2),Battery,1S Li-ion/LiPo with JST-PH 2.0 plug,,,-,Not on board. Check plug polarity vs + / - silkscreen before connecting
39,1,(J4),LoRa antenna,SMA antenna for chosen band,,,-,Not on board
40,1,(J3),GPS antenna,"Active GNSS antenna, U.FL",,,-,Not on board. VCC_RF bias is applied via L1
